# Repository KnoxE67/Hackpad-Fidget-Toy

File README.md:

# MacroPad Overview

This project requires a Seeed XIAO RP2040, 
6 MX-Style switches, 
1 EC11 Rotary encoder, 
1 0.91 inch OLED display, 
6 Blank DSA keycaps (White), 
4 M3x16mm screws, 
4 M3x5mx4mm heatset inserts,
and a top and bottom 3d printed case.

## Pictures

| Schematic | PCB | Case |
|:-:|:-:|:-:|
|  |  |  |

## Bill of Materials (BOM)

- 1x XIAO RP2040
- 6x MX-like switches
- 6x DSA keycaps
- 1x 0.91" 128x32 OLED display
- 1x EC11E rotary encoder
- 1x case, made of 2 printed parts ([Top.step](pictures/top.step) and [Bottom.step](pictures/bottom.step) )
- 4x M3x16mm screws
- 4x M3x5mx4mm heatset inserts

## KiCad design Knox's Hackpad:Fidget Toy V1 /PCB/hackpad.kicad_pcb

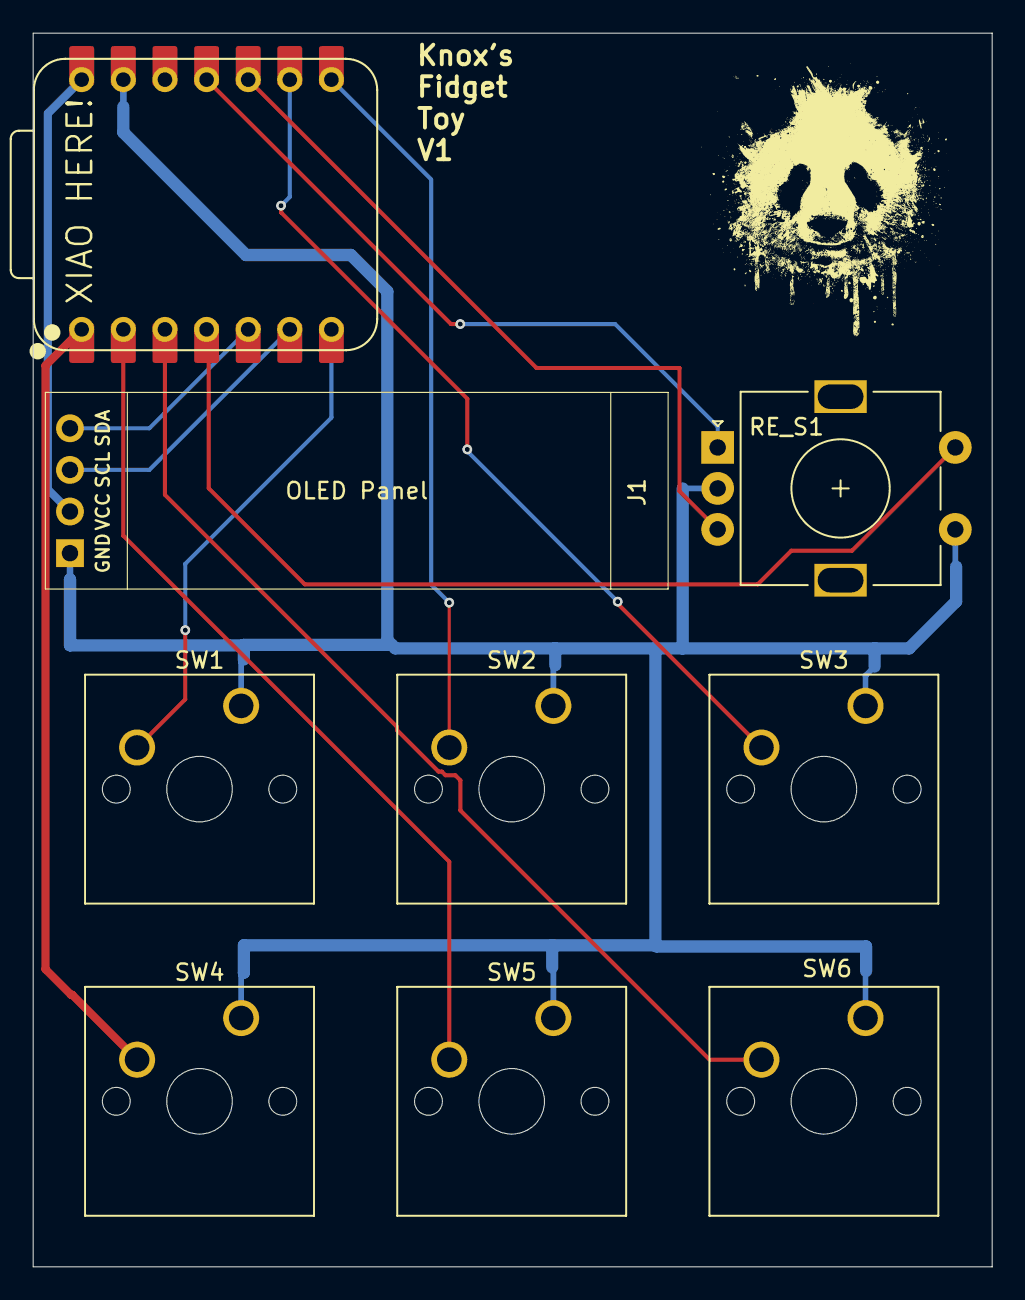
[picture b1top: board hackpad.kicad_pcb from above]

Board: 2 copper layers, 58.5 x 75.3 mm, 9 parts (0 on the bottom side), 13 nets.

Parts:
J1: OLED DISPLAY; SSD1306-0.91-OLED-4pin-128x32
RE_S1: RotaryEncoder_Switch; RotaryEncoder_Alps_EC11E-Switch_Vertical_H20mm
SW1, SW2, SW3, SW4, SW5, SW6: SW_Push; SW_Cherry_MX_1.00u_PCB
U1: XIAO-RP2040-DIP

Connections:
+5V: J1.2, U1.14 (VBUS)
GND: J1.1, RE_S1.C, RE_S1.S1, SW1.1, SW2.1, SW3.1, SW4.1, SW5.1, SW6.1, U1.13 (GND)
R_A: RE_S1.A, U1.11 (GPIO3/MOSI)
R_B: RE_S1.B, U1.10 (GPIO4/MISO)
R_ESW: RE_S1.S2, U1.4 (GPIO29/ADC3/A3)
SCL: J1.3, U1.6 (GPIO7/SCL)
SDA: J1.4, U1.5 (GPIO6/SDA)
SW_1: SW1.2, U1.7 (GPIO0/TX)
SW_2: SW2.2, U1.8 (GPIO1/RX)
SW_3: SW3.2, U1.9 (GPIO2/SCK)
SW_4: SW4.2, U1.1 (GPIO26/ADC0/A0)
SW_5: SW5.2, U1.2 (GPIO27/ADC1/A1)
SW_6: SW6.2, U1.3 (GPIO28/ADC2/A2)

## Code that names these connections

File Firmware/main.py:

import board
import busio
import displayio
import terminalio
import microcontroller
import adafruit_displayio_ssd1306
import time

from kmk.extensions.media_keys import MediaKeys
from adafruit_display_text import label
from kmk.kmk_keyboard import KMKKeyboard
from kmk.scanners.keypad import KeysScanner
from kmk.keys import KC
from kmk.modules.macros import Macros
from kmk.modules.encoder import EncoderHandler

# --- 1. OLED Setup ---
displayio.release_displays()
# Using the GPIO labels from your schematic
i2c = busio.I2C(microcontroller.pin.GPIO7, microcontroller.pin.GPIO6)
display_bus = displayio.I2CDisplay(i2c, device_address=0x3C)
display = adafruit_displayio_ssd1306.SSD1306(display_bus, width=128, height=32)

splash = displayio.Group()
display.root_group = splash

header_lbl = label.Label(terminalio.FONT, text="Knox's Hackpad", x=0, y=5)
status_lbl = label.Label(terminalio.FONT, text="MODE: MACRO", x=0, y=16)
vol_lbl = label.Label(terminalio.FONT, text="VOL: [|||||-----] 50%", x=0, y=27)

splash.append(header_lbl)
splash.append(status_lbl)
splash.append(vol_lbl)

def update_oled_vol(level, muted):
    if muted:
        vol_lbl.text = "VOL: [ MUTED X ]"
    else:
        filled = level // 10
        bar = "|" * filled + "-" * (10 - filled)
        vol_lbl.text = f"VOL: [{bar}] {level}%"

# --- 2. Keyboard Setup ---
keyboard = KMKKeyboard()
macros = Macros()
keyboard.modules.append(macros)
keyboard.extensions.append(MediaKeys())

# --- 3. Encoder Setup ---
encoder_handler = EncoderHandler()
keyboard.modules.append(encoder_handler)

# FIXED DIRECTION: Swapped GPIO4 and GPIO3
# Original: (GPIO4, GPIO3...) -> Now: (GPIO3, GPIO4...)
encoder_handler.pins = ((microcontroller.pin.GPIO3, microcontroller.pin.GPIO4, microcontroller.pin.GPIO29, False),)
encoder_handler.divisor = 4

# --- 4. Matrix Setup ---
PINS = [
    microcontroller.pin.GPIO0, microcontroller.pin.GPIO1, microcontroller.pin.GPIO2, 
    microcontroller.pin.GPIO26, microcontroller.pin.GPIO27, microcontroller.pin.GPIO28
]
keyboard.matrix = KeysScanner(pins=PINS, value_when_pressed=False)

# --- 5. Keymap ---
# FIXED DELETE: Changed KC.DELETE to KC.BSPC (Backspace) for standard deleting
keyboard.keymap = [[
    KC.ESC, KC.LCMD(KC.SPC), KC.BSPC,
    KC.LCMD(KC.C), KC.LCMD(KC.V), KC.ENTER,
]]
encoder_handler.map = [((KC.VOLU, KC.VOLD, KC.MUTE),)]

# --- 6. Custom Logic Module ---
class HackpadModule:
    def __init__(self):
        self.vol_level = 50
        self.is_muted = False
        self.last_activity = time.monotonic()
        self.is_sleeping = False
        self.timeout = 300 

    def wake(self):
        if self.is_sleeping:
            display.wake()
            self.is_sleeping = False
        self.last_activity = time.monotonic()

    def before_matrix_scan(self, keyboard):
        if not self.is_sleeping and (time.monotonic() - self.last_activity > self.timeout):
            display.sleep()
            self.is_sleeping = True

    def on_runtime_enable(self, keyboard): 
        update_oled_vol(self.vol_level, self.is_muted)

    def deinit(self, keyboard): pass
    def on_runtime_disable(self, keyboard): pass
    def during_bootup(self, keyboard): pass
    def after_matrix_scan(self, keyboard): pass
    def before_hid_send(self, keyboard): pass
    def after_hid_send(self, keyboard): pass

    def after_key_handler(self, keyboard, key, is_pressed):
        if is_pressed:
            self.wake()
            # Precise key detection for your specific keymap
            if key == KC.LCMD(KC.C): status_lbl.text = "COPYING..."
            elif key == KC.LCMD(KC.V): status_lbl.text = "PASTING..."
            elif key == KC.F4: status_lbl.text = "SEARCHING..."
            elif key == KC.ENTER: status_lbl.text = "ENTERING..."
            elif key == KC.BSPC: status_lbl.text = "DELETING..."
            elif key == KC.ESC: status_lbl.text = "ESCAPING..."
            
            # Encoder Logic
            if key == KC.VOLU:
                self.is_muted = False
                self.vol_level = min(100, self.vol_level + 5)
            elif key == KC.VOLD:
                self.is_muted = False
                self.vol_level = max(0, self.vol_level - 5)
            elif key == KC.MUTE:
                self.is_muted = not self.is_muted
            
            update_oled_vol(self.vol_level, self.is_muted)
        else:
            status_lbl.text = "MODE: MACRO"

keyboard.modules.append(HackpadModule())

if __name__ == '__main__':
    keyboard.go()

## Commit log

2026-01-10 Add README
2026-01-10 added pictures
2026-01-10 removed folder
2026-01-11 added top and bottom photos
2026-01-11 added firmware/main.py
2026-01-12 added both top and bottom case step files
2026-01-13 added pcb .step file
2026-01-14 changed what the screen says in main.py
2026-01-17 updated the code
2026-01-18 updated some code
2026-01-27 fixed code
